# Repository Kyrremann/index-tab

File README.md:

Index Tab
---------

 Index Tab is a 6x13 ortho keyboard. Tried to make it look like index tab that are used as dividers in drawers and
 ring binders. The reason for 13 in width instead of 12 is that I’m Norwegian, and neeed that added row for `æøå`.

 You can play around with the layout over at [Keyboard Layout Editor](http://www.keyboard-layout-editor.com/#/gists/2577189f7cf19d980fff8177d14dc3ec).

## Diary

### [rev5] - 2021-03-07

It's over a year since I started on this project. I had problem soldering rev4, so decided to copy the MCU laytout from
[evyd13/plain60-c](https://github.com/evyd13/plain60-c) and pay for SMT assembly. I also had to fix the spacer holes,
as they where too small for the spacers. The size was for a M2 screw. It's been changed to a 5mm hole. The OLED screen
has also been removed, firstly because I choose the wrong component (so the holes where way too small), and I don't
really like the look of the OLED screens.

Another big change is the change to the keyboard layout, I've removed the swiss cheeze bottom. Decided to just go for a
simple 1u only row, 2x2u, or 7u bottom-row. Now you can use clip-in stabilizers. Does didn't fit the swiss cheese row.

### [rev4] - 2020-06-10

The original plan was to be done with the project with revision 3, but looking at what I wanted to use the keyboard for,
I decided to add a OLED screen to it. By doing that I could make a cool and simple keyboard switcher, with information
about each switch. Will probably be a lot of work to get that to work, so we'll see if it ever will be made.

Another thing I wanted to try out, as can be seen in PCB and layout images, is the swiss cheese bottom row. It started
with me adding the stabs hole that should have been in rev1, and then adding more and more, too see if it is possible!
And yes, it is possible with a lot of holes, the issue I've discovedred now, is that the stabs are not fitting as good,
because there are so many hole next to each other, and overlapping.

There will be one more revision before I'm saying I'm done, but that will just be to fix the small m2 screw holes for
mounting, that should have been m2 spacers holes. Major mistake there...

### [rev2] - 2020-04-10

It's going slow, like most of the world right now. I ordered the second revision before I managed to get the first one
working as I was a bit afraid there where something wrong with my design, plus I was sick and tired of debugging it.

Revision 2 was ordered 30th of March, and it arrived a week after that, and it took me until now to write how it's
gone. I can start of by saying it finally work! It didn't work at first, and it didn't work before I changed the
capacitators for the crystal to something lower. I had originally just used the same crystal and capacitators as the
[UT47.2](https://github.com/ai03-2725/UT47.2/), but it turnes out to not work for the bigger ATMEGA-32U4 chip (compared
to the smaller ATMEGA-32U2 chip). After good tips from both Slack and Discord, I tried a lower capacitator, going from
22pF down to 14pF, which is more correct if your using a "Load Capacitance formula", check out this
[Adafruit](https://blog.adafruit.com/2012/01/24/choosing-the-right-crystal-and-caps-for-your-design/) article to learn
more.

From the image below you can see that I haven't made a proper case for it yet, mostly because I'm not used to working
with Inkscape, but I should be able to make a sandwich case with the tab on the top, other then that it's not much more
to do for the Index Tab. I am planning a third revision, adding arrows for the diode silk print, adding holes for the
stabs, and maybe making the space bar "area" more customizable.

### [rev1] - 2020-02-28

Yesterday I received the PCB for my first keyboard. It's looks better then expected, and I'm pleased with the form
factor that I choose. I also had time to solder the important bits, aka the micro controller, to see if it works.

Sadly, it looks like it doesn't. There is no connection with the Atmega-chip, and I have no idea why. There are 
several possibilities for this, so I need to do further debugging. One highly plausible reason is that there is 
bad connection with the crystal, as the footprint I choose doesn't really fit with the crystal that I ordered.

Another thing I found out is that I used a 0603 foot print for my diodes, instead of the normal SOD-123, so
that is at least one thing that needs to be fixed in the next version.

I've also decided to drop  the schottky-diode, as it turns out I really don't need it. I'm also thorn about
keeping the power led that I've added. It's nice to see that the board is powered, but it's also pretty visible
if you have RGB-leds, or just by typing. It kinda just add to the design, without being necessary.

Another foot print that I want to change is the USB-C, as I'd like to order all parts from DigiKey, instead of
ordering the USB-C from LCSC and the rest from DigiKey.

Other then that there are some minor design changes I would like to do. Align all the RGBs with each other, and align
all the diode at the bottom of the foot prints for the switches. Also, the holes for the switch legs where really(!) 
thight. That should probably need to be fixed.

That's all for now. Probably going to make a seperate blog for my keyboards, as I want to write about the
[Akihabare 40](https://www.thingiverse.com/thing:3105838) and [Apoptosis](https://github.com/pseudoku/Apoptosis)
keyboards I ordered at the same time as my Index Tab.

### Renders

For now I've got some simple renders from Kicad, enjoy!

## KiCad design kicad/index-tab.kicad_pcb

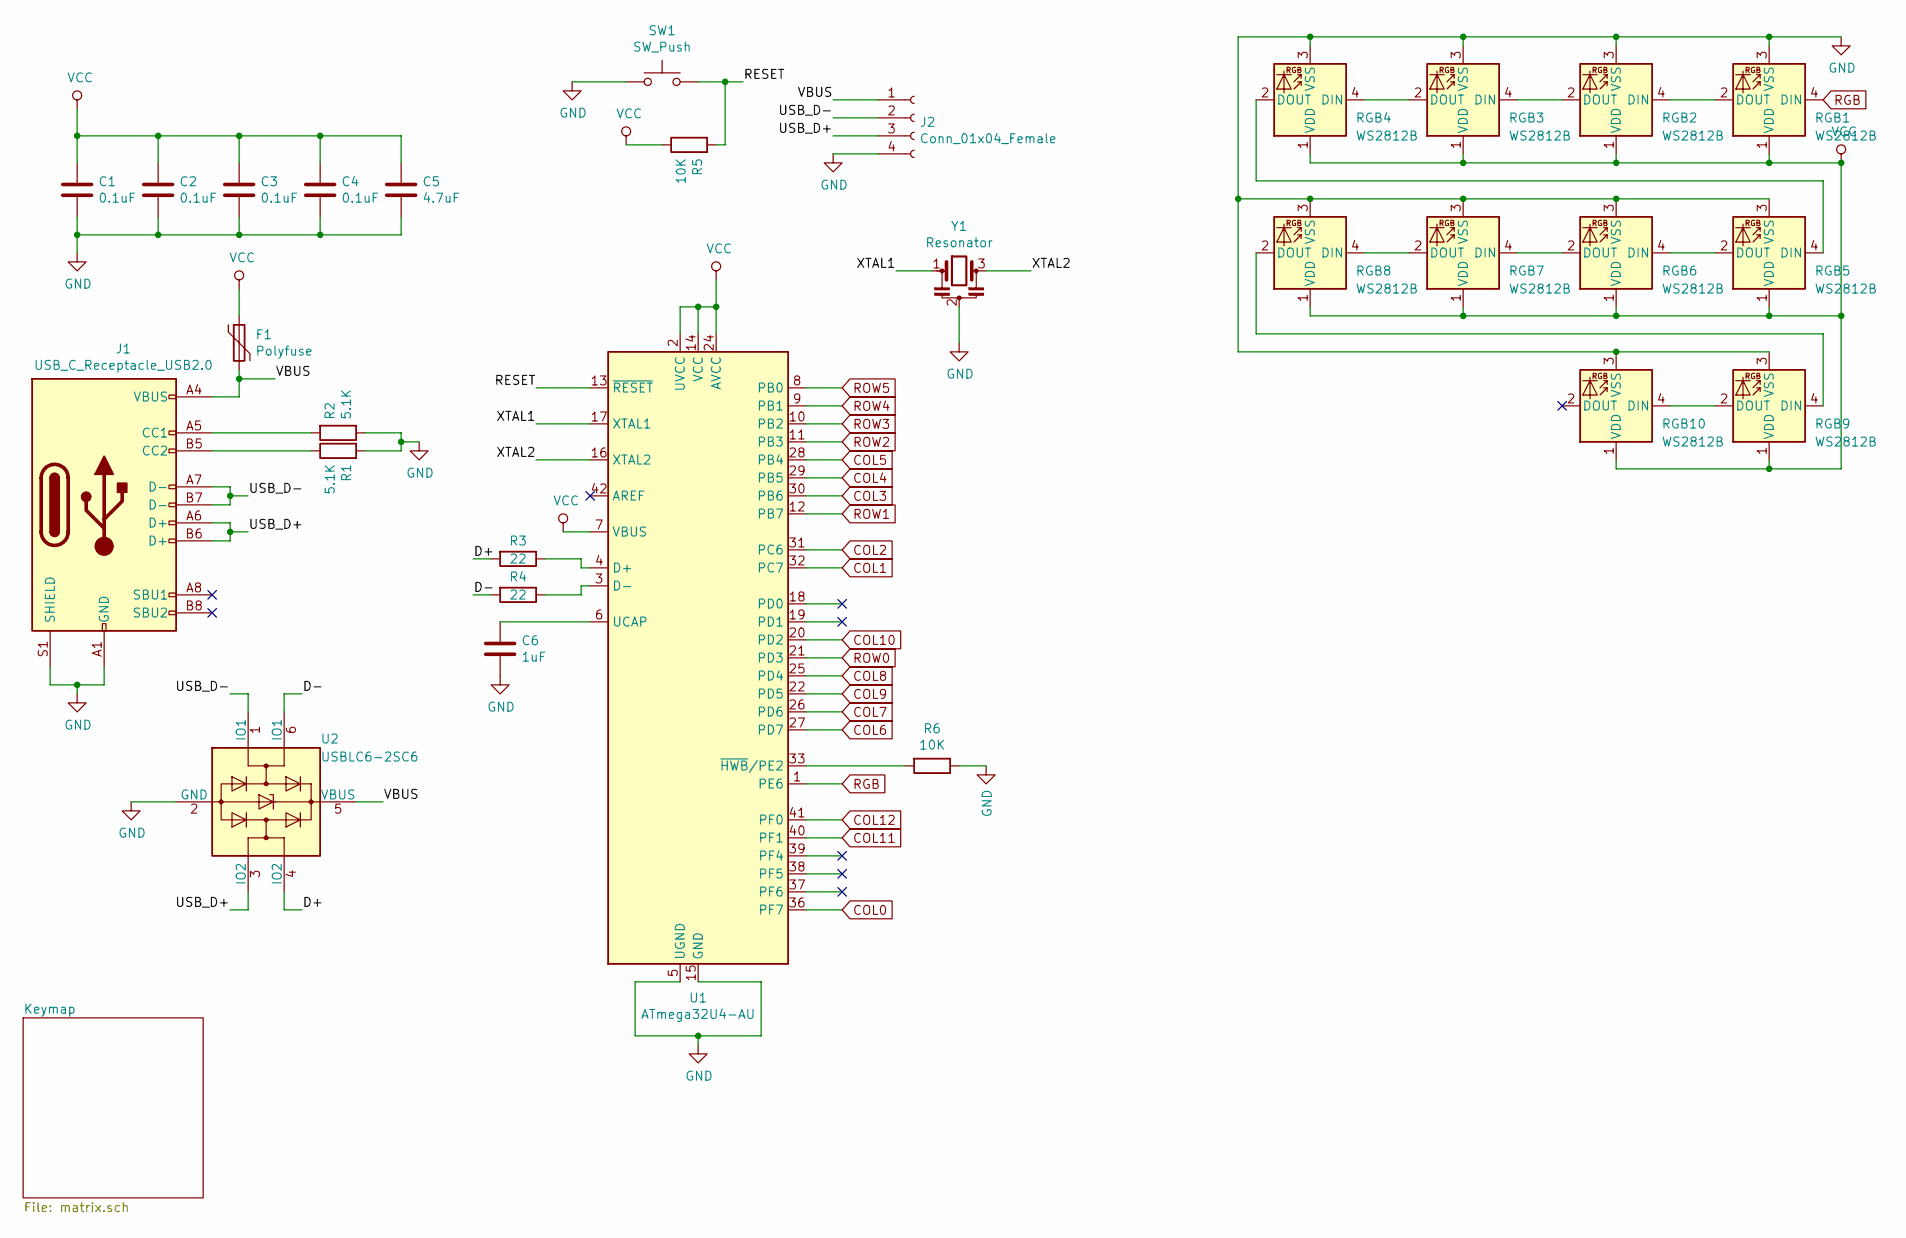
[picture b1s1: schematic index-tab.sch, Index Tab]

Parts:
C1, C2, C3, C4: 0.1uF; C_0603_1608Metric
C5: 4.7uF; C_0603_1608Metric
C6: 1uF; C_0603_1608Metric
F1: Polyfuse; Fuse_0603_1608Metric
J1: USB_C_Receptacle_USB2.0; USB_C_Receptacle_HRO_TYPE-C-31-M-12
J2: Conn_01x04_Female; JST_SH_SM04B-SRSS-TB_1x04-1MP_P1.00mm_Horizontal
R1, R2: 5.1K; R_0603_1608Metric
R3, R4: 22; R_0603_1608Metric
R5, R6: 10K; R_0603_1608Metric
RGB1, RGB2, RGB3, RGB4, RGB5, RGB6, RGB7, RGB8, RGB9, RGB10: WS2812B; LED_WS2812B_PLCC4_5.0x5.0mm_P3.2mm
SW1: SW_Push; SW_DIP_SPSTx01_Slide_6.7x4.1mm_W6.73mm_P2.54mm_LowProfile_J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
U1: ATmega32U4-AU; TQFP-44_10x10mm_P0.8mm
U2: USBLC6-2SC6; SOT-23-6
Y1: Resonator; Resonator_SMD_muRata_CSTxExxV-3Pin_3.0x1.1mm_HandSoldering

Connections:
/D+: R3.2, U2.4 (IO2)
/D-: R4.2, U2.6 (IO1)
/RESET: R5.2, SW1.2, U1.13 (~RESET)
/USB_D+: J1.A6 (D+), J1.B6 (D+), J2.3, U2.3 (IO2)
/USB_D-: J1.A7 (D-), J1.B7 (D-), J2.2, U2.1 (IO1)
/VBUS: F1.2, J1.A4 (VBUS), J1.A9 (VBUS), J1.B4 (VBUS), J1.B9 (VBUS), J2.1, U2.5 (VBUS)
/XTAL1: U1.17 (XTAL1), Y1.1
/XTAL2: U1.16 (XTAL2), Y1.3
COL0: U1.36 (PF7); also elsewhere on the board
COL1: U1.32 (PC7); also elsewhere on the board
COL2: U1.31 (PC6); also elsewhere on the board
COL3: U1.30 (PB6); also elsewhere on the board
COL4: U1.29 (PB5); also elsewhere on the board
COL5: U1.28 (PB4); also elsewhere on the board
COL6: U1.27 (PD7); also elsewhere on the board
COL7: U1.26 (PD6); also elsewhere on the board
COL8: U1.25 (PD4); also elsewhere on the board
COL9: U1.22 (PD5); also elsewhere on the board
COL10: U1.20 (PD2); also elsewhere on the board
COL11: U1.40 (PF1); also elsewhere on the board
COL12: U1.41 (PF0); also elsewhere on the board
GND: C1.2, C2.2, C3.2, C4.2, C5.2, C6.1, J1.A1 (GND), J1.A12 (GND), J1.B1 (GND), J1.B12 (GND), J1.S1 (SHIELD), J2.4, R1.2, R2.1, R6.1, RGB1.3 (VSS), RGB2.3 (VSS), RGB3.3 (VSS), RGB4.3 (VSS), RGB5.3 (VSS), RGB6.3 (VSS), RGB7.3 (VSS), RGB8.3 (VSS), RGB9.3 (VSS), RGB10.3 (VSS), SW1.1, U1.5 (UGND), U1.15 (GND), U1.23 (GND), U1.35 (GND), U1.43 (GND), U2.2 (GND), Y1.2
unnamed: C6.2, U1.6 (UCAP)
unnamed: J1.A5 (CC1), R2.2
unnamed: J1.B5 (CC2), R1.1
unnamed: R3.1, U1.4 (D+)
unnamed: R4.1, U1.3 (D-)
unnamed: R6.2, U1.33 (~HWB~/PE2)
unnamed: RGB1.2 (DOUT), RGB2.4 (DIN)
unnamed: RGB2.2 (DOUT), RGB3.4 (DIN)
unnamed: RGB3.2 (DOUT), RGB4.4 (DIN)
unnamed: RGB4.2 (DOUT), RGB5.4 (DIN)
unnamed: RGB5.2 (DOUT), RGB6.4 (DIN)
unnamed: RGB6.2 (DOUT), RGB7.4 (DIN)
unnamed: RGB7.2 (DOUT), RGB8.4 (DIN)
unnamed: RGB8.2 (DOUT), RGB9.4 (DIN)
unnamed: RGB9.2 (DOUT), RGB10.4 (DIN)
RGB: RGB1.4 (DIN), U1.1 (PE6)
ROW0: U1.21 (PD3); also elsewhere on the board
ROW1: U1.12 (PB7); also elsewhere on the board
ROW2: U1.11 (PB3); also elsewhere on the board
ROW3: U1.10 (PB2); also elsewhere on the board
ROW4: U1.9 (PB1); also elsewhere on the board
ROW5: U1.8 (PB0); also elsewhere on the board
VCC: C1.1, C2.1, C3.1, C4.1, C5.1, F1.1, R5.1, RGB1.1 (VDD), RGB2.1 (VDD), RGB3.1 (VDD), RGB4.1 (VDD), RGB5.1 (VDD), RGB6.1 (VDD), RGB7.1 (VDD), RGB8.1 (VDD), RGB9.1 (VDD), RGB10.1 (VDD), U1.2 (UVCC), U1.7 (VBUS), U1.14 (VCC), U1.24 (AVCC), U1.34 (VCC), U1.44 (AVCC)

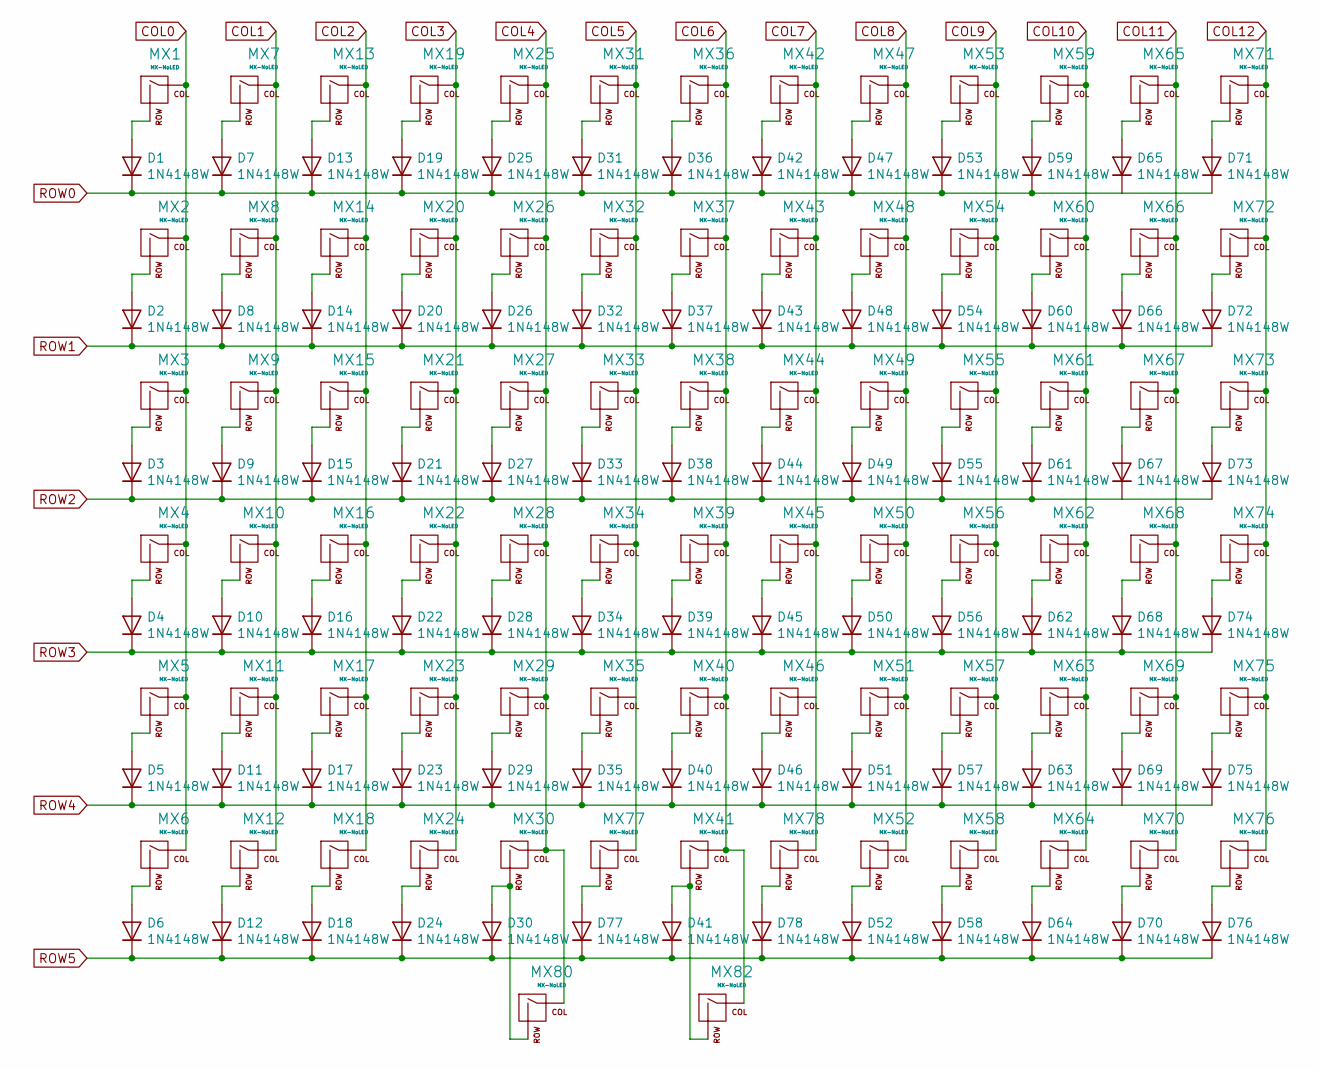
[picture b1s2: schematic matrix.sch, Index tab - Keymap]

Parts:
D1, D2, D3, D4, D5, D6, D7, D8, D9, D10, D11, D12, D13, D14, D15, D16, D17, D18, D19, D20, D21, D22, D23, D24, D25, D26, D27, D28, D29, D30, D31, D32, D33, D34, D35, D36, D37, D38, D39, D40, D41, D42, D43, D44, D45, D46, D47, D48, D49, D50, D51, D52, D53, D54, D55, D56, D57, D58, D59, D60, D61, D62, D63, D64, D65, D66, D67, D68, D69, D70, D71, D72, D73, D74, D75, D76, D77, D78: 1N4148W; D_SOD-123
MX1, MX2, MX3, MX4, MX5, MX6, MX7, MX8, MX9, MX10, MX11, MX12, MX13, MX14, MX15, MX16, MX17, MX18, MX19, MX20, MX21, MX22, MX23, MX24, MX25, MX26, MX27, MX28, MX29, MX30, MX31, MX32, MX33, MX34, MX35, MX36, MX37, MX38, MX39, MX40, MX41, MX42, MX43, MX44, MX45, MX46, MX47, MX48, MX49, MX50, MX51, MX52, MX53, MX54, MX55, MX56, MX57, MX58, MX59, MX60, MX61, MX62, MX63, MX64, MX65, MX66, MX67, MX68, MX69, MX70, MX71, MX72, MX73, MX74, MX75, MX76, MX77, MX78, MX80, MX82: MX-NoLED; Kailh_socket_MX

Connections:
COL0: MX1.1 (COL), MX2.1 (COL), MX3.1 (COL), MX4.1 (COL), MX5.1 (COL), MX6.1 (COL); also elsewhere on the board
COL1: MX7.1 (COL), MX8.1 (COL), MX9.1 (COL), MX10.1 (COL), MX11.1 (COL), MX12.1 (COL); also elsewhere on the board
COL2: MX13.1 (COL), MX14.1 (COL), MX15.1 (COL), MX16.1 (COL), MX17.1 (COL), MX18.1 (COL); also elsewhere on the board
COL3: MX19.1 (COL), MX20.1 (COL), MX21.1 (COL), MX22.1 (COL), MX23.1 (COL), MX24.1 (COL); also elsewhere on the board
COL4: MX25.1 (COL), MX26.1 (COL), MX27.1 (COL), MX28.1 (COL), MX29.1 (COL), MX30.1 (COL), MX80.1 (COL); also elsewhere on the board
COL5: MX31.1 (COL), MX32.1 (COL), MX33.1 (COL), MX34.1 (COL), MX35.1 (COL), MX77.1 (COL); also elsewhere on the board
COL6: MX36.1 (COL), MX37.1 (COL), MX38.1 (COL), MX39.1 (COL), MX40.1 (COL), MX41.1 (COL), MX82.1 (COL); also elsewhere on the board
COL7: MX42.1 (COL), MX43.1 (COL), MX44.1 (COL), MX45.1 (COL), MX46.1 (COL), MX78.1 (COL); also elsewhere on the board
COL8: MX47.1 (COL), MX48.1 (COL), MX49.1 (COL), MX50.1 (COL), MX51.1 (COL), MX52.1 (COL); also elsewhere on the board
COL9: MX53.1 (COL), MX54.1 (COL), MX55.1 (COL), MX56.1 (COL), MX57.1 (COL), MX58.1 (COL); also elsewhere on the board
COL10: MX59.1 (COL), MX60.1 (COL), MX61.1 (COL), MX62.1 (COL), MX63.1 (COL), MX64.1 (COL); also elsewhere on the board
COL11: MX65.1 (COL), MX66.1 (COL), MX67.1 (COL), MX68.1 (COL), MX69.1 (COL), MX70.1 (COL); also elsewhere on the board
COL12: MX71.1 (COL), MX72.1 (COL), MX73.1 (COL), MX74.1 (COL), MX75.1 (COL), MX76.1 (COL); also elsewhere on the board
unnamed: D1.2 (A), MX1.2 (ROW)
unnamed: D2.2 (A), MX2.2 (ROW)
unnamed: D3.2 (A), MX3.2 (ROW)
unnamed: D4.2 (A), MX4.2 (ROW)
unnamed: D5.2 (A), MX5.2 (ROW)
unnamed: D6.2 (A), MX6.2 (ROW)
unnamed: D7.2 (A), MX7.2 (ROW)
unnamed: D8.2 (A), MX8.2 (ROW)
unnamed: D9.2 (A), MX9.2 (ROW)
unnamed: D10.2 (A), MX10.2 (ROW)
unnamed: D11.2 (A), MX11.2 (ROW)
unnamed: D12.2 (A), MX12.2 (ROW)
unnamed: D13.2 (A), MX13.2 (ROW)
unnamed: D14.2 (A), MX14.2 (ROW)
unnamed: D15.2 (A), MX15.2 (ROW)
unnamed: D16.2 (A), MX16.2 (ROW)
unnamed: D17.2 (A), MX17.2 (ROW)
unnamed: D18.2 (A), MX18.2 (ROW)
unnamed: D19.2 (A), MX19.2 (ROW)
unnamed: D20.2 (A), MX20.2 (ROW)
unnamed: D21.2 (A), MX21.2 (ROW)
unnamed: D22.2 (A), MX22.2 (ROW)
unnamed: D23.2 (A), MX23.2 (ROW)
unnamed: D24.2 (A), MX24.2 (ROW)
unnamed: D25.2 (A), MX25.2 (ROW)
unnamed: D26.2 (A), MX26.2 (ROW)
unnamed: D27.2 (A), MX27.2 (ROW)
unnamed: D28.2 (A), MX28.2 (ROW)
unnamed: D29.2 (A), MX29.2 (ROW)
unnamed: D30.2 (A), MX30.2 (ROW), MX80.2 (ROW)
unnamed: D31.2 (A), MX31.2 (ROW)
unnamed: D32.2 (A), MX32.2 (ROW)
unnamed: D33.2 (A), MX33.2 (ROW)
unnamed: D34.2 (A), MX34.2 (ROW)
unnamed: D35.2 (A), MX35.2 (ROW)
unnamed: D36.2 (A), MX36.2 (ROW)
unnamed: D37.2 (A), MX37.2 (ROW)
unnamed: D38.2 (A), MX38.2 (ROW)
unnamed: D39.2 (A), MX39.2 (ROW)
unnamed: D40.2 (A), MX40.2 (ROW)
unnamed: D41.2 (A), MX41.2 (ROW), MX82.2 (ROW)
unnamed: D42.2 (A), MX42.2 (ROW)
unnamed: D43.2 (A), MX43.2 (ROW)
unnamed: D44.2 (A), MX44.2 (ROW)
unnamed: D45.2 (A), MX45.2 (ROW)
unnamed: D46.2 (A), MX46.2 (ROW)
unnamed: D47.2 (A), MX47.2 (ROW)
unnamed: D48.2 (A), MX48.2 (ROW)
unnamed: D49.2 (A), MX49.2 (ROW)
unnamed: D50.2 (A), MX50.2 (ROW)
unnamed: D51.2 (A), MX51.2 (ROW)
unnamed: D52.2 (A), MX52.2 (ROW)
unnamed: D53.2 (A), MX53.2 (ROW)
unnamed: D54.2 (A), MX54.2 (ROW)
unnamed: D55.2 (A), MX55.2 (ROW)
unnamed: D56.2 (A), MX56.2 (ROW)
unnamed: D57.2 (A), MX57.2 (ROW)
unnamed: D58.2 (A), MX58.2 (ROW)
unnamed: D59.2 (A), MX59.2 (ROW)
unnamed: D60.2 (A), MX60.2 (ROW)
unnamed: D61.2 (A), MX61.2 (ROW)
unnamed: D62.2 (A), MX62.2 (ROW)
unnamed: D63.2 (A), MX63.2 (ROW)
unnamed: D64.2 (A), MX64.2 (ROW)
unnamed: D65.2 (A), MX65.2 (ROW)
unnamed: D66.2 (A), MX66.2 (ROW)
unnamed: D67.2 (A), MX67.2 (ROW)
unnamed: D68.2 (A), MX68.2 (ROW)
unnamed: D69.2 (A), MX69.2 (ROW)
unnamed: D70.2 (A), MX70.2 (ROW)
unnamed: D71.2 (A), MX71.2 (ROW)
unnamed: D72.2 (A), MX72.2 (ROW)
unnamed: D73.2 (A), MX73.2 (ROW)
unnamed: D74.2 (A), MX74.2 (ROW)
unnamed: D75.2 (A), MX75.2 (ROW)
unnamed: D76.2 (A), MX76.2 (ROW)
unnamed: D77.2 (A), MX77.2 (ROW)
unnamed: D78.2 (A), MX78.2 (ROW)
ROW0: D1.1 (K), D7.1 (K), D13.1 (K), D19.1 (K), D25.1 (K), D31.1 (K), D36.1 (K), D42.1 (K), D47.1 (K), D53.1 (K), D59.1 (K), D65.1 (K), D71.1 (K); also elsewhere on the board
ROW1: D2.1 (K), D8.1 (K), D14.1 (K), D20.1 (K), D26.1 (K), D32.1 (K), D37.1 (K), D43.1 (K), D48.1 (K), D54.1 (K), D60.1 (K), D66.1 (K), D72.1 (K); also elsewhere on the board
ROW2: D3.1 (K), D9.1 (K), D15.1 (K), D21.1 (K), D27.1 (K), D33.1 (K), D38.1 (K), D44.1 (K), D49.1 (K), D55.1 (K), D61.1 (K), D67.1 (K), D73.1 (K); also elsewhere on the board
ROW3: D4.1 (K), D10.1 (K), D16.1 (K), D22.1 (K), D28.1 (K), D34.1 (K), D39.1 (K), D45.1 (K), D50.1 (K), D56.1 (K), D62.1 (K), D68.1 (K), D74.1 (K); also elsewhere on the board
ROW4: D5.1 (K), D11.1 (K), D17.1 (K), D23.1 (K), D29.1 (K), D35.1 (K), D40.1 (K), D46.1 (K), D51.1 (K), D57.1 (K), D63.1 (K), D69.1 (K), D75.1 (K); also elsewhere on the board
ROW5: D6.1 (K), D12.1 (K), D18.1 (K), D24.1 (K), D30.1 (K), D41.1 (K), D52.1 (K), D58.1 (K), D64.1 (K), D70.1 (K), D76.1 (K), D77.1 (K), D78.1 (K); also elsewhere on the board

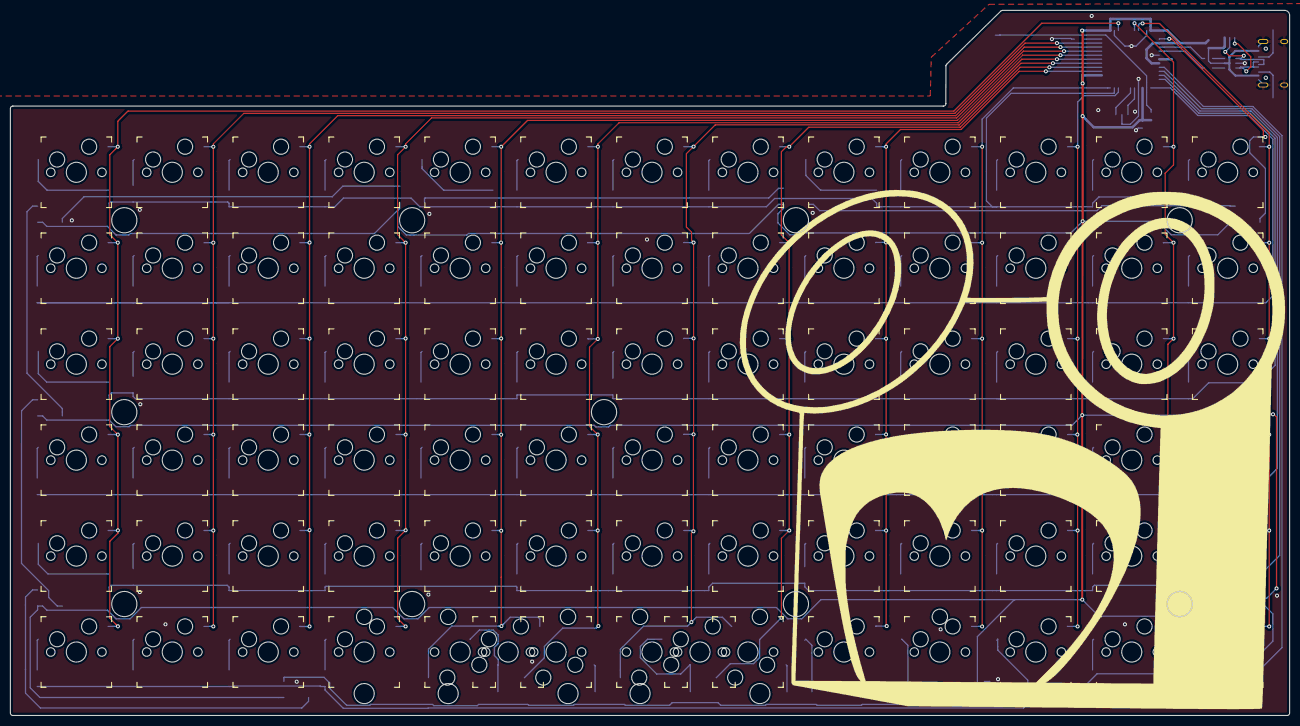
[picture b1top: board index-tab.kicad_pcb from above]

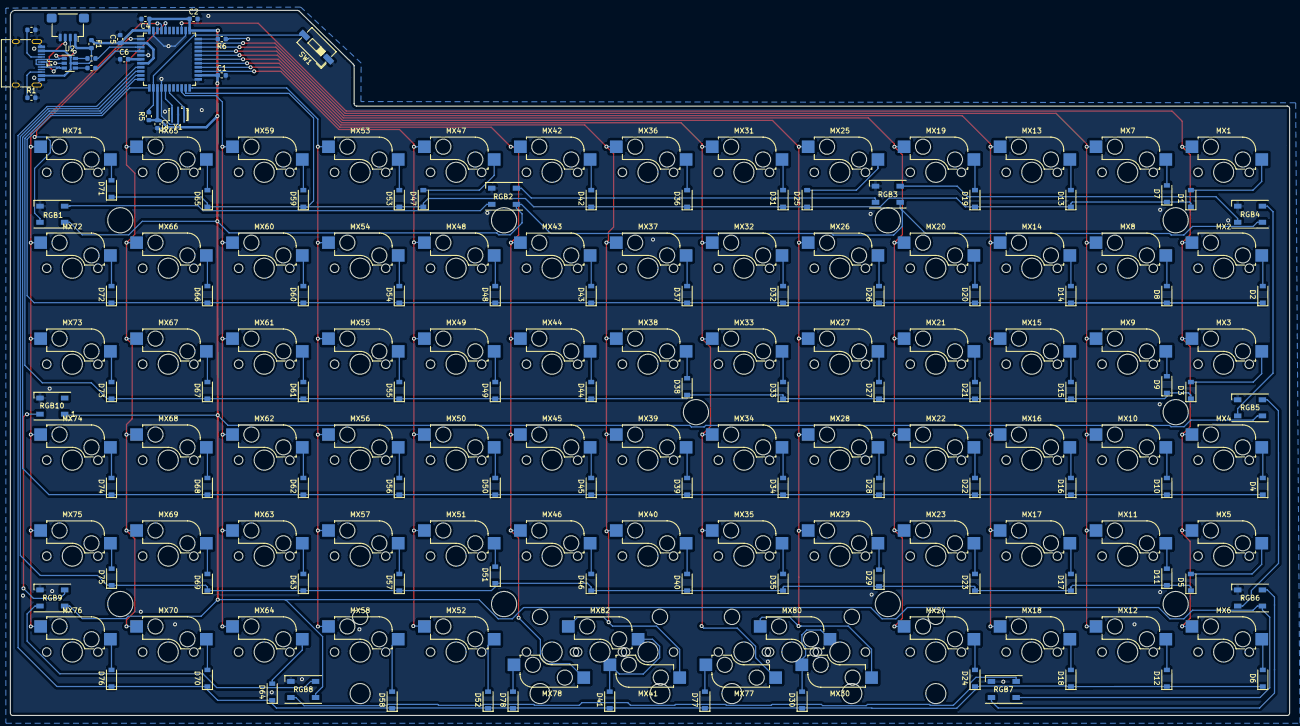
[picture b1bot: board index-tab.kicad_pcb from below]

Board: 2 copper layers, 254.0 x 140.0 mm, 190 parts (107 on the bottom side), 123 nets.

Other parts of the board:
STAB1: 7u; MXOnly-7U-Hotswap
STAB2, STAB3: 2u; Stabilizer_MX_2u

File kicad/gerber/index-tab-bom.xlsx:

Comment | Designator | Footprint | LCSC Part Number
0.1uF | C1, C2, C3, C4 | Capacitor_SMD:C_0603_1608Metric | C14663
4.7uF | C5 | Capacitor_SMD:C_0603_1608Metric | C19666
1uF | C6 | Capacitor_SMD:C_0603_1608Metric | C15849
1N4148W | D1, D7, D13, D19, D25, D31, D36, D42, D47, D53, D59, D65, D71, D2, D8, D14, D20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 | Diode_SMD:D_SOD-123 | C81598
Polyfuse | F1 | Fuse:Fuse_0603_1608Metric | C70046
USB_C_Receptacle_USB2 | J1 | Connector_USB:USB_C_Receptacle_HRO_TYPE-C-31-M-12 | C165948
5.1K | R2, R1 | Resistor_SMD:R_0603_1608Metric | C23186
22 | R4, R3 | Resistor_SMD:R_0603_1608Metric | C23345
10K | R5, R6 | Resistor_SMD:R_0603_1608Metric | C25804
WS2812B | RGB1, RGB4, RGB3, RGB2, RGB5, RGB6, RGB7, RGB8, RGB9, RGB10 | LED_SMD:LED_WS2812B_PLCC4_5.0x5.0mm_P3.2mm | C114583
SW_Push | SW1 | Button_Switch_SMD:SW_DIP_SPSTx01_Slide_6.7x4.1mm_W6.73mm_P2.54mm_LowProfile_JPin | C318938
ATmega32U4-AU | U1 | Package_QFP:TQFP-44_10x10mm_P0.8mm | C44854
USBLC6-2SC6 | U2 | Package_TO_SOT_SMD:SOT-23-6 | C7519
Resonator | Y1 | Crystal:Resonator_SMD_muRata_CSTxExxV-3Pin_3.0x1.1mm_HandSoldering | C341521

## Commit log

2020-02-06 Init commit
    Started small, with atmega-chip and usb-c. Not sure if it's working, but it's a start.
2020-02-06 possible keymap
2020-02-07 Updated somevalues, and fixed the pin layout
2020-02-09 Added MX alps hybrid symbol to the library
2020-02-09 Trying to make the library path indepented
2020-02-09 Change to u4, added files for backlight and rgb
2020-02-10 changed some labels, and hopefully done with the atmega32u4 changes
2020-02-10 added backlight and rgb
2020-02-10 managed to remove the cache
2020-02-10 Added footprints to all components, and done some formatting
2020-02-17 Working PCB, plus images
2020-02-17 Moved images to theire own folder
2020-02-17 Renamed folder
2020-02-17 Added some more text
2020-02-17 Should not be here
2020-02-19 Not SOT-143B footprint in Kicad
2020-02-19 Switched to 0603 and redrawn the PCB
2020-02-19 Added rounded corners to the pcb
2020-02-19 Moved some components for better fillzone
2020-02-19 Added RGB and a monster to the f.silk
2020-02-19 Updated the images to latest version
2020-02-28 Latest changes before v0.1 was sent to production
2020-02-28 The gerber sent to production
2020-02-28 Wrote about the first production run v0.1
2020-02-28 It's SOD, not SOT
2020-02-29 Changed diode footprint to the more used sod-123
2020-02-29 Moved diode and rgb footprint
    Need to create new traces too, but later
2020-03-04 Retraced and rebuild the PCB
    Fixed wrong footprint for diodes and crystal. Trying out a new USB-C, but probably changing back before order of rev2. Also added ESD for safty.
2020-03-05 the image is of type jpg
2020-03-06 Changed USB-C and added more gnd
    Suing the easier HRO TYPE-C-31-M-12
2020-03-08 rev2 ordered
    this was done before I've managed to get rev1 working. Post coming about it. rev2 looks more like UT47.2
2020-04-20 Old updated, finally pushed out
2020-04-28 wrong image name
2020-04-28 it was a png image
2020-05-02 Added stabs and fixed text
2020-05-03 rotated all the rgb so they face the same direction
2020-05-03 Added screw holes to the board
    Will make it easier to make better cases
2020-05-03 Updated images for rev3
2020-05-03 Fixed ugly trace
2020-05-03 Updated gerber for rev3
2020-05-11 added revision number
2020-05-11 added bom for all three revisions
2020-05-23 Adding crazy many options for bottom row
    this is going to be rev4
2020-05-24 finished adding stabs
    There is no way to many possiblities at the bottom row
2020-05-24 OLED screen added
2020-05-24 Changed the mountin hole
    Can now have a seperate plate for the oled/top. Also added the monster head back in
2020-05-24 Updated images
2020-06-10 Updated KLE with rev4
2020-06-10 Wrote about rev4
2021-02-12 rev4: I think
    This is so old I'm not really sure what it is. Going to make rev5 anyway, so just ignore this.
2021-02-12 rev5: updated schematic
    This is heavily inspired by Plain60 by evyd13
2021-02-13 rev5: MCU schematic and pcb should be done
2021-02-13 rev5: fixed 2x2u and 7u stabs
2021-02-14 rev5: fixed mounting holes
    This time they are of the correct size for spacers!
2021-02-14 rev5: minor fixes after feedback
    Flipped 2u switch, as that will probably be main layout, so no problems with gateron switches
    Some vias was a bit to close to diodes
    Made gnd pads for jst bigger for easier soldering
2021-02-14 rev5: ready for production
2021-03-07 rev5: added images and diary page
2021-03-07 rev5: updated kicard renders
2021-03-07 rev5: updated bom
2021-03-07 rev5: files should just be in the release
2021-03-07 doc: spelling mistake
2021-10-10 feat: added case files
